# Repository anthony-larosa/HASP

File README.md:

# HASP

This provides a general outline of working documentation of the design and integration of a micro-spectrometer into a handheld device.

The spectrometer used is a Hamamatsu C12880MA micro-spectrometer, enclosures were designed using SolidWorks, the spectrometer was controlled using a STM32F4 ARM based microcontroller. Firmware was written in C and data analysis provided was done using Matlab and Python.

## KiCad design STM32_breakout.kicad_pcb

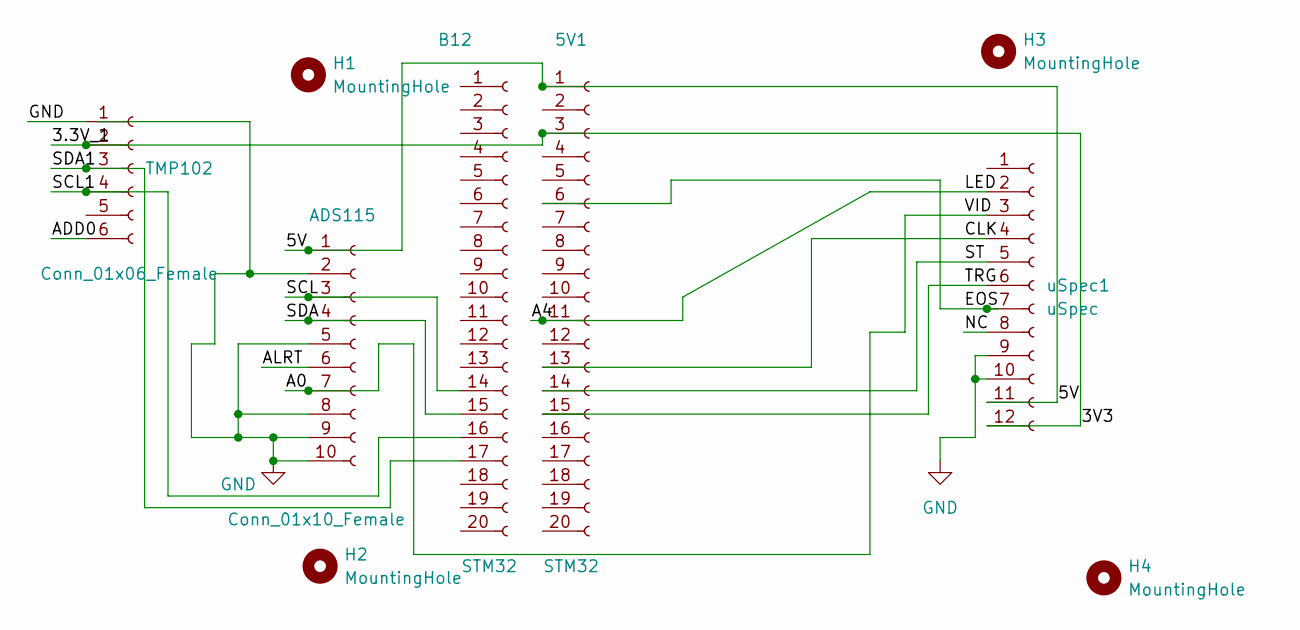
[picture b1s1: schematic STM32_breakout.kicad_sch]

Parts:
5V1: STM32; PinSocket_1x20_P2.54mm_Vertical
ADS115: Conn_01x10_Female
B12: STM32; PinSocket_1x20_P2.54mm_Vertical
H1, H2, H3, H4: MountingHole; MountingHole_3mm
TMP102: Conn_01x06_Female
uSpec1: uSpec; PinSocket_1x12_P2.54mm_Vertical

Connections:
/3.3V_1: 5V1.3, TMP102.2, uSpec1.12
/5V: 5V1.1, ADS115.1, uSpec1.11
/A0: ADS115.7, uSpec1.3
/ADD0: TMP102.6
/ALRT: ADS115.6
/CLK: 5V1.13, uSpec1.4
/EOS: 5V1.6, uSpec1.7
/LED: 5V1.11, uSpec1.2
/NC: uSpec1.8
/SCL: ADS115.3, B12.14
/SCL1: B12.16, TMP102.4
/SDA: ADS115.4, B12.15
/SDA1: B12.17, TMP102.3
/ST: 5V1.14, uSpec1.5
/TRG: 5V1.15, uSpec1.6
GND: ADS115.2, ADS115.5, ADS115.8, ADS115.9, ADS115.10, TMP102.1, uSpec1.9, uSpec1.10

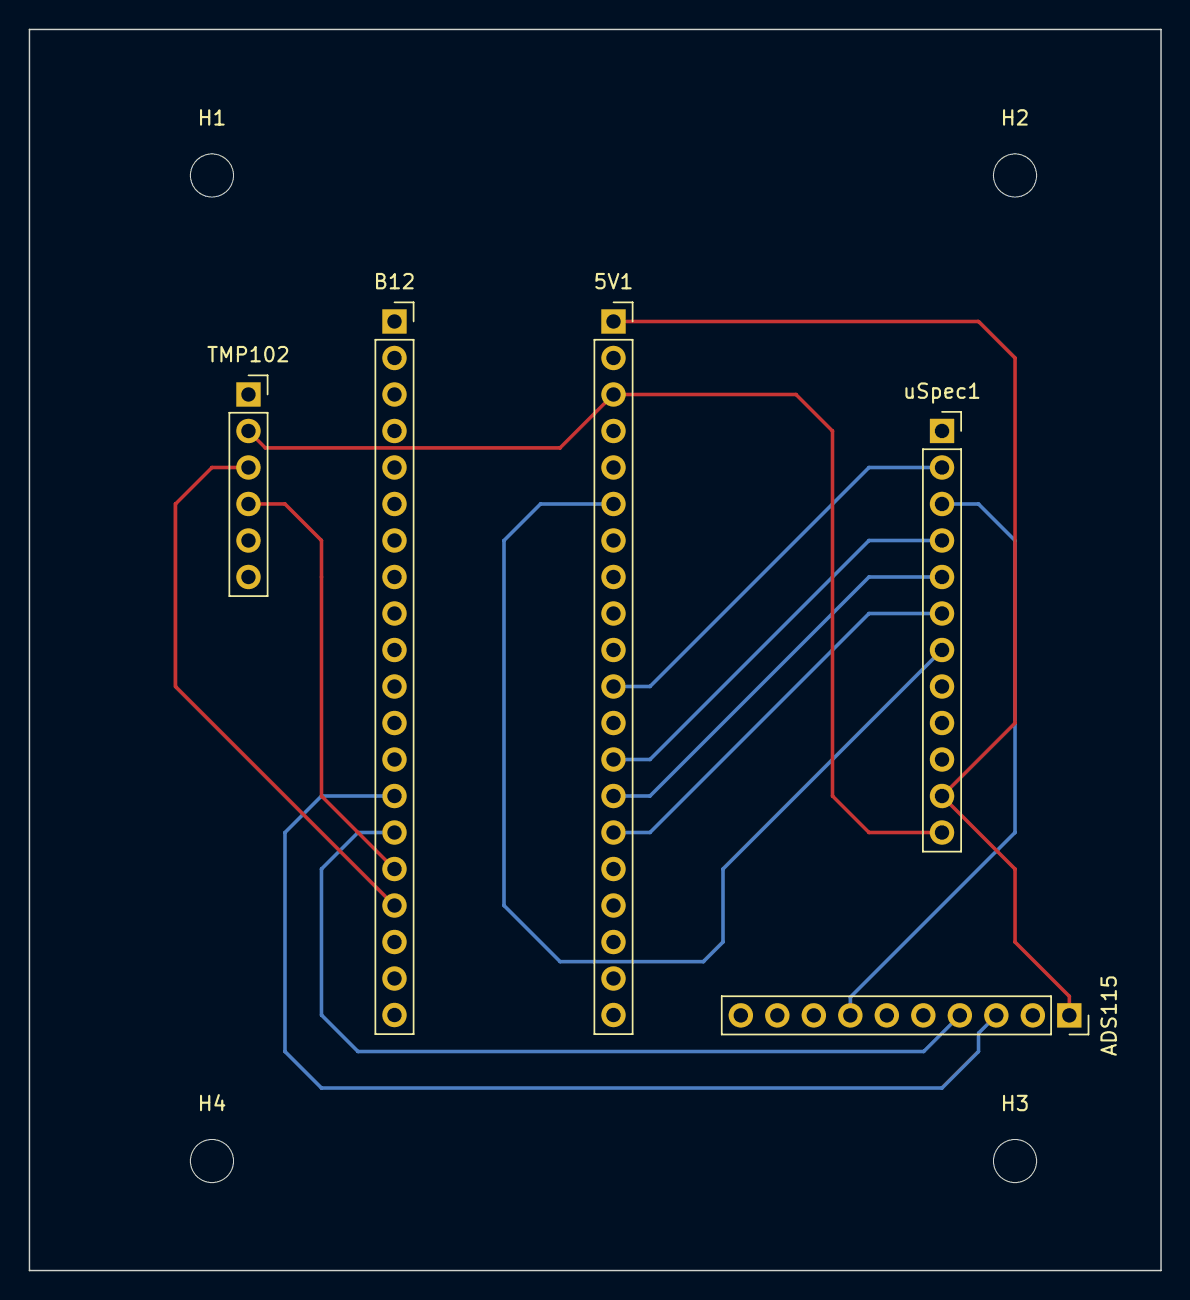
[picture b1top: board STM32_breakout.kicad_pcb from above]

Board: 2 copper layers, 78.7 x 86.4 mm, 9 parts (0 on the bottom side), 13 nets.

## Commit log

2022-10-22 New file
2022-10-22 Rename STM32_breakout.kicad_pcb to ECAD/STM32_breakout.kicad_pcb
2022-10-22 Rename STM32_breakout.kicad_prl to ECAD/STM32_breakout.kicad_prl
2022-10-22 Rename STM32_breakout.kicad_pro to ECAD/STM32_breakout.kicad_pro
2022-10-22 Rename STM32_breakout.kicad_sch to ECAD/STM32_breakout.kicad_sch
2022-10-22 Rename calibration_black_pill.c to firmware/calibration_black_pill.c
2022-10-22 Rename device_run.c to firmware/device_run.c
